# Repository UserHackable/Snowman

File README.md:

## Snowman 

### Board dimensions

* (150000, 230000) original units
* (1.5000, 2.3000) inches
* (38.1000, 58.4200) mm

| Front | Back |
| --- | --- |
|  |  |

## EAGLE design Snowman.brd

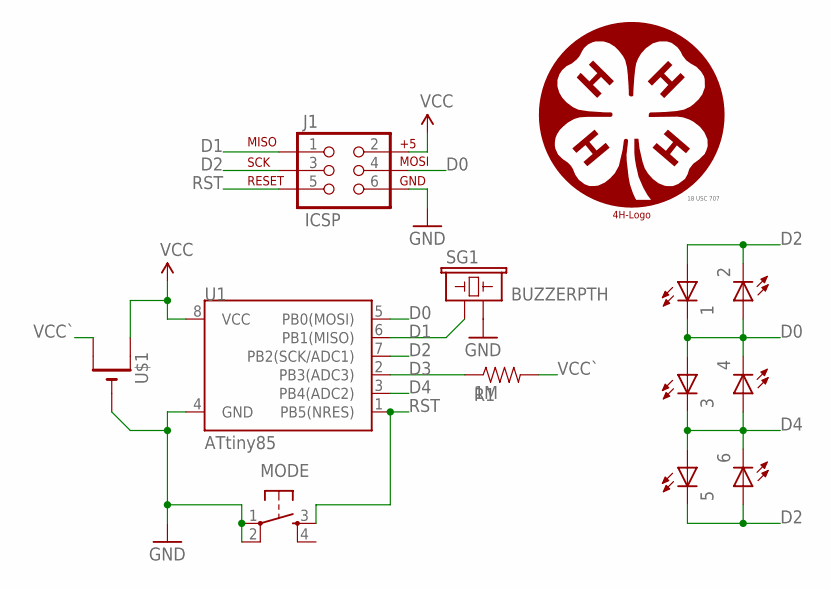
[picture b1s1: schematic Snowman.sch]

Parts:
1, 2, 3, 4, 5, 6: LEDOVAL; LED-OVAL
J1: ICSP; 2X3-NS
MODE: TAC_SWITCHPTH; TACTILE-PTH
R1: 1M; AXIAL-0.3
SG1: BUZZERPTH; BUZZER-12MM
U1: ATtiny85; DIP08
U$1: CR2032THM; CR2032-THRU
U$2: 18 USC 707; 4H_LOGO_6

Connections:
D0: 1.CATHODE (C), 2.ANODE (A), 3.ANODE (A), 4.CATHODE (C), J1.4 (MOSI), U1.5 (PB0(MOSI))
D1: J1.1 (MISO), SG1.+ (1), U1.6 (PB1(MISO))
D2: 1.ANODE (A), 2.CATHODE (C), 5.CATHODE (C), 6.ANODE (A), J1.3 (SCK), U1.7 (PB2(SCK/ADC1))
D3: R1.P$1 (1), U1.2 (PB3(ADC3))
D4: 3.CATHODE (C), 4.ANODE (A), 5.ANODE (A), 6.CATHODE (C), U1.3 (PB4(ADC2))
GND: J1.6 (GND), MODE.1, MODE.2, SG1.- (2), U1.4 (GND), U$1.-
RST: J1.5 (RST), MODE.3, U1.1 (PB5(NRES))
VCC: J1.2 (V+), U1.8 (VCC), U$1.+1 (+)
VCC`: R1.P$2 (2), U$1.+2 (+1)

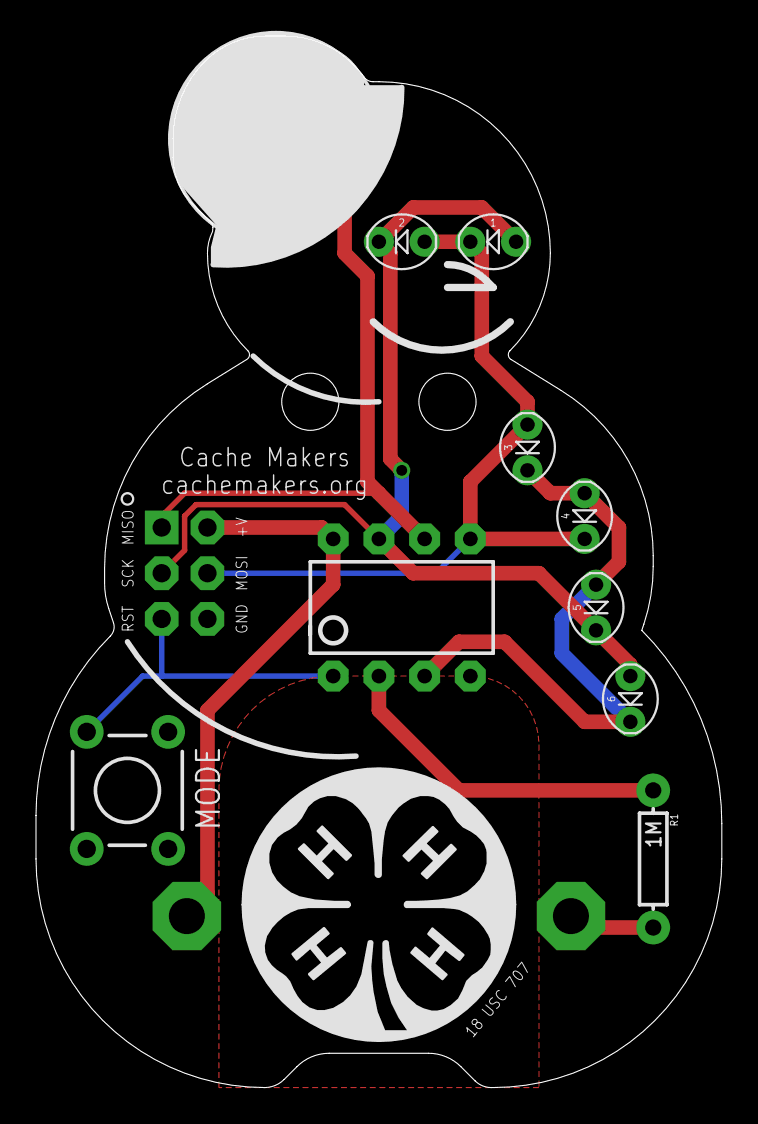
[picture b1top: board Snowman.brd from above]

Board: 2 copper layers, 38.1 x 58.4 mm, 13 parts (1 on the bottom side), 9 nets.

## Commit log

2016-04-06 updating images
2016-04-06 updating board layout
2016-04-06 updating adding pullup
2016-04-06 4H logo
2016-04-07 from Makefile

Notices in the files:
parts and their libraries:
SparkFun-Electromechanical: Licensing: Creative Commons ShareAlike 4.0 International - https://creativecommons.org/licenses/by-sa/4.0
